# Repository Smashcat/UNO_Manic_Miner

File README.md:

# Arduino UNO Game Engine
Manic Miner, Scramble and Space Invaders on the Arduino UNO with composite output

This is a project to demonstrate the use of my game engine, with a port of Manic Miner, originally for the ZX Spectrum, by Matthew Smith, and the original Scramble and Space Invaders arcade machine, it also now has the console game Pacman Championship Edition. Please note that this is for the original Arduino UNO with the ATMega328P microcontroller - it will not work on any other versions of the Arduino. Also, some of the cheaper "Arduino compatible" boards use resonators instead of crystals for their clock. These are nowhere near accurate enough to generate the video signal. I have tried several and it caused extreme jitter in the image. If you can, use an official Arduino, or at least a board with a proper 16Mhz crystal!!

## Engine Features:

+ Composite output using 2 resistors
+ Scrolling tilemap background
+ Up to 9 16x16 sprites on screen, with up to 7 per scanline
+ 1 sprite has pixel-perfect collision detection against other sprites
+ Fixed framerate of 50fps
+ Effective resolution is 256x256 (no framebuffer, everything is generated by "racing the beam")
+ Lots of spare cycles, enough to run game logic and easily update sprite positions, and even all tile indexes on screen every frame!

## PCB Features:
  
+ PCB design schematics for a shield for the Arduino UNO, with buttons, composite output, speaker driving circuit and a an area to mount a Nintendo NES controller port to use instead of the buttons
+ All files for PCB, including production files ready to place a fully assembled order (except for the NES port and header pins) from JLCPCB. Cost including delivery per board for 20 fully assembled boards seems to be around £4 for me in the UK.

## Manic Miner Game Features:

+ All 20 original levels
+ All "special" boss and other mechanics. Including Eugene, the Kong Beast, Skylab crashing enemies and Solar Generator beam
+ Extra animation on final cavern level showing realtime tile animation
+ Menu screen with options to choose start level, turn music on/off and reset high score which is persistant between boots
+ 2 channel audio with original music
+ Special end screen and message if you complete the game!

## Space Invaders Game Features:

+ Pixel perfect recreation of original graphics
+ Gameplay logic matches the original game
+ Persistant high score (can be reset by holding Option+Start at boot)
+ 2 Channel Audio

## Scramble Game Features

+ Level data from original ROMs
+ Gameplay logic matches original game
+ Smooth pixel scrolling, with fixed starfield in background
+ Persistant high score (can be reset by holding Start at boot)
+ 2 Channel Audio

## Pacman Championsip Edition Features

+ Fast moving gameplay with smooth pixel scrolling
+ Optimized graphics for the 1-bit display
+ 2 Channel PWM audio, with sound effects closely matching original Pacman game
+ High score list (hold SELECT+START at power on to reset list)
+ [WebASM demo available! ](https://www.smashcat.org/pacman-ce/)

## YouTube:

## Screen-shots:

### CRT monitor:

### TFT TV screen:

### PCB shield with NES controller

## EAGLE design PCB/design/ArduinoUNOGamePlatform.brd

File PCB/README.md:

# Arduino UNO Manic Miner

Composite output shield for Arduino UNO

This folder contains the files for the PCB that can be used with this project.

+ ./design - the Eagle design files
+ ./images - Schematic and board images
+ ./production-files - These can be used to have the PCB fully assembled at JLCPCB. If using another service, the gerbers should be compatible.

I have also linked sources I used for the NES controller and port that can be soldered to the PCB, below. Also the 3 pin jack to 2 x RCA cable I use for video and audio connection from the PCB to my TV/monitors. I'm not sponsored by anyone, just thought these might be handy!

## NES port compatible with the PCB:

## NES controller (aftermarket) - make sure you pick the "nes white" or "nes grey" version, NOT the "classic mini" version!:

## 3-pin 3.5mm jack to 2xRCA male cable:

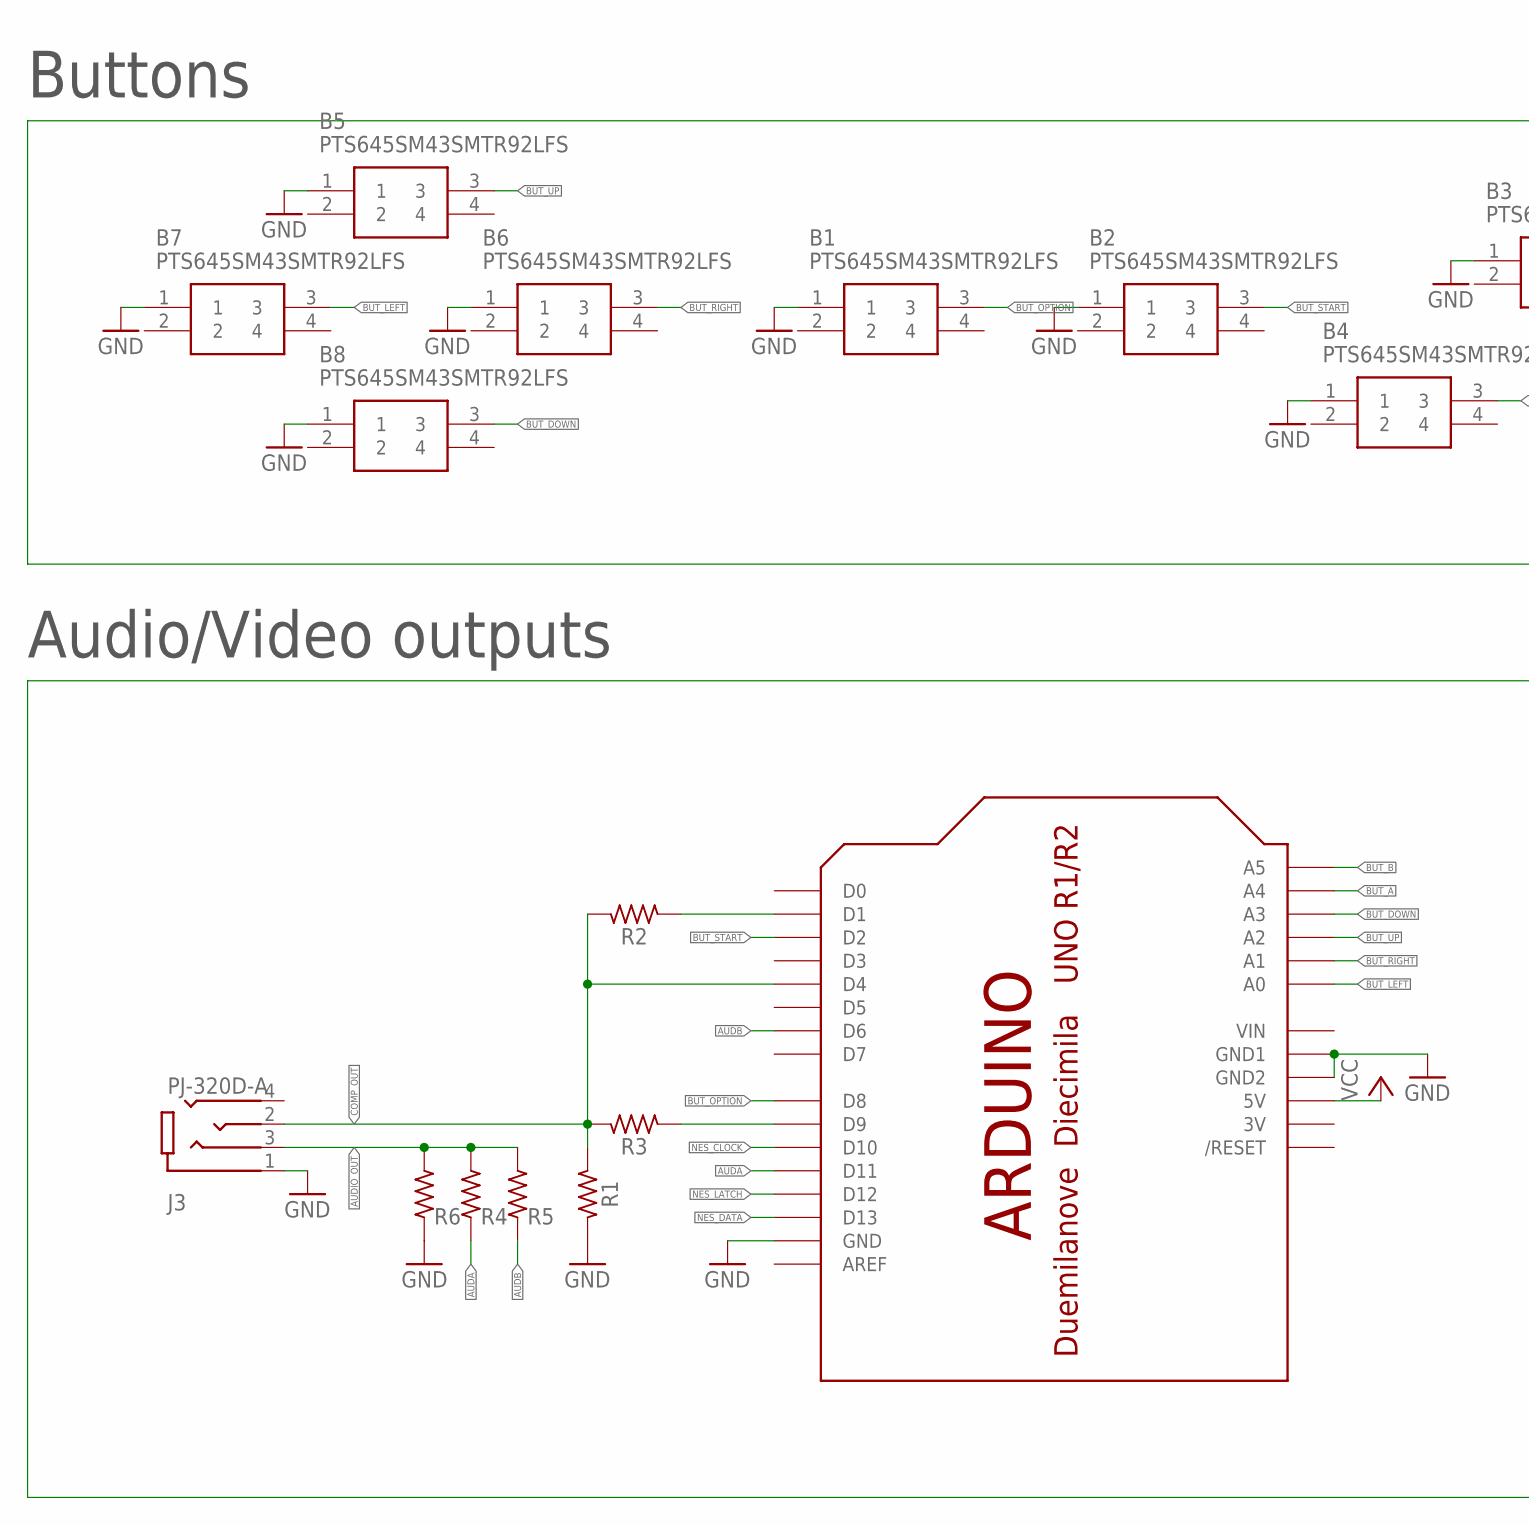
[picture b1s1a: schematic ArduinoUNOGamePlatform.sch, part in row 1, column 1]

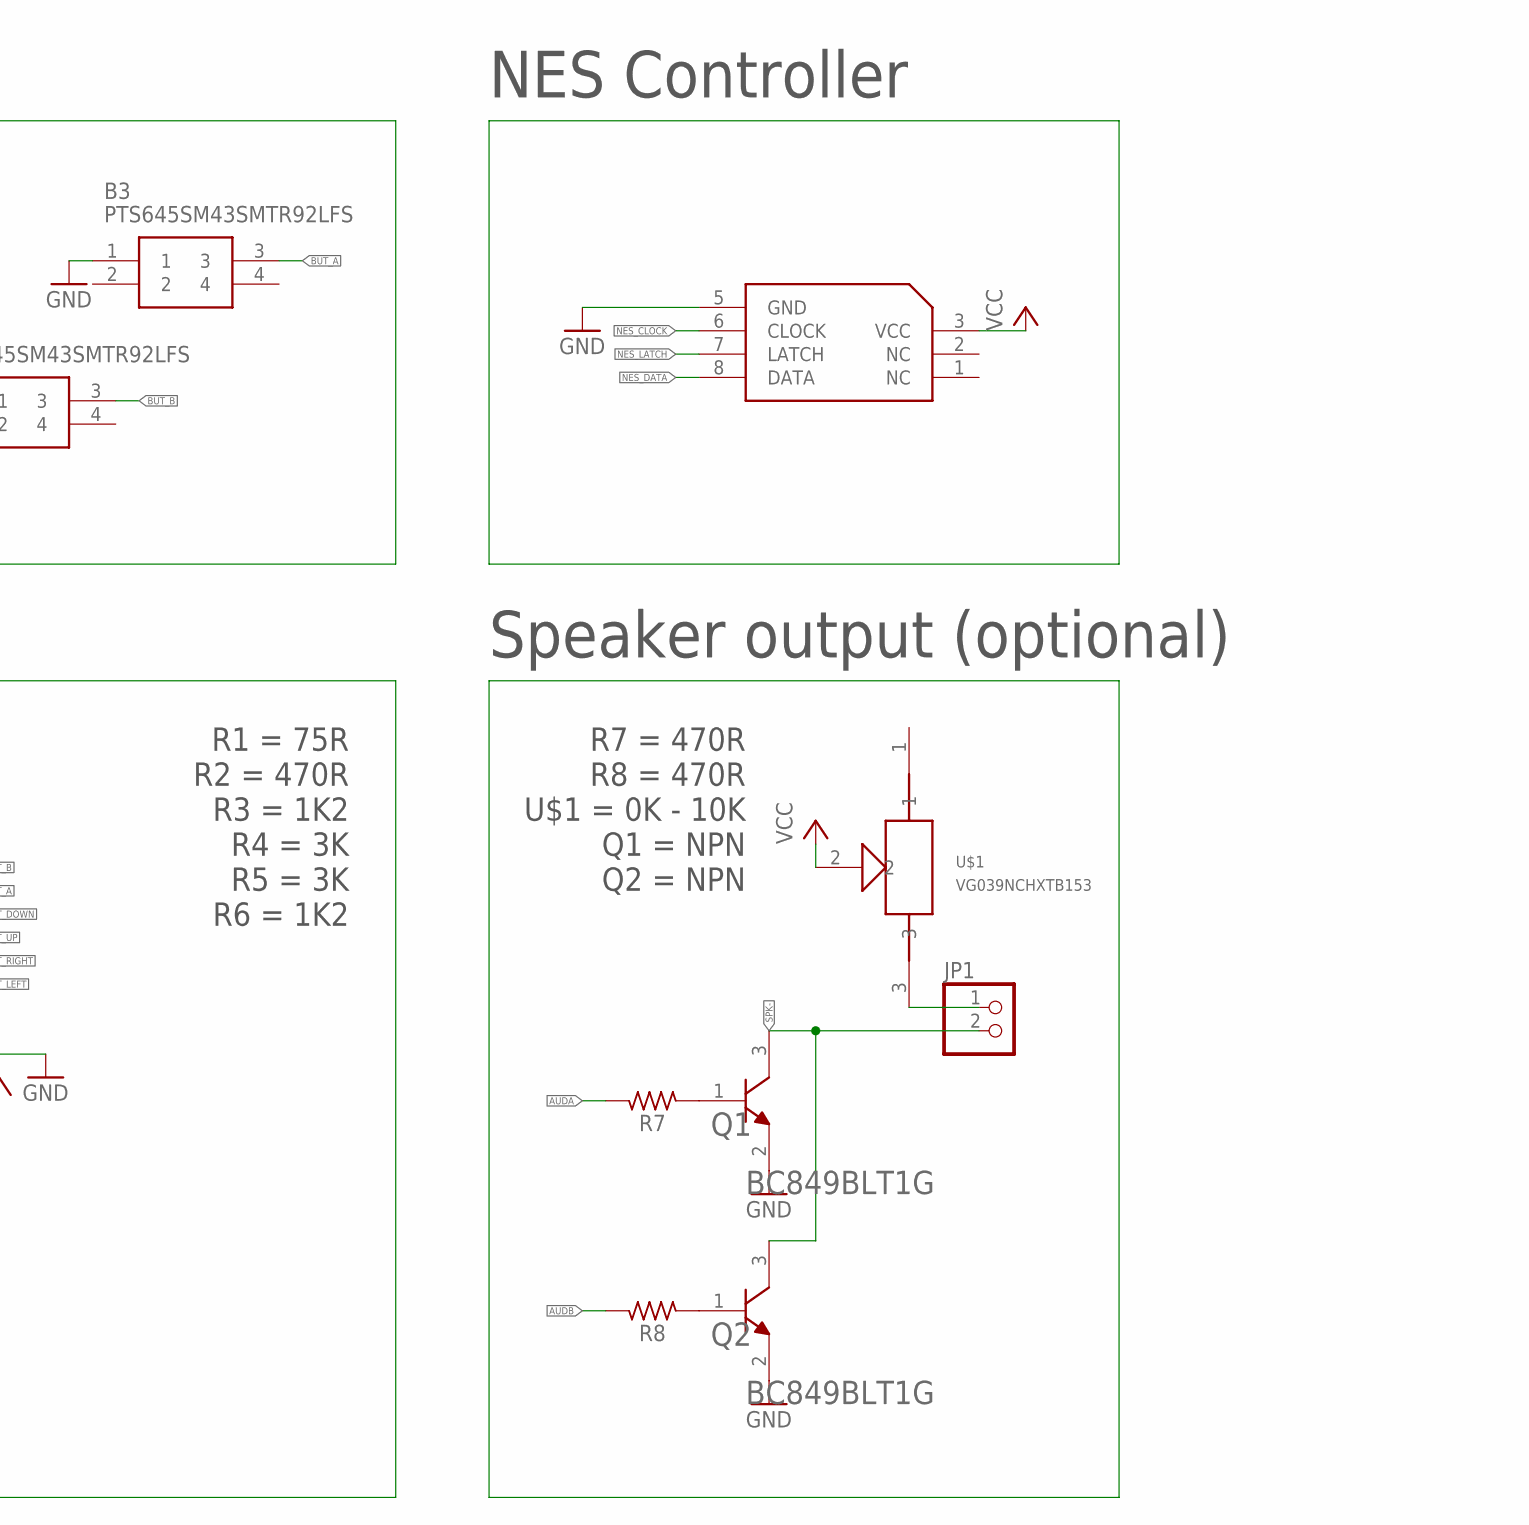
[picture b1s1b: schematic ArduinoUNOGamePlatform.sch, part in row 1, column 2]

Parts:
B1, B2, B3, B4, B5, B6, B7, B8: PTS645SM43SMTR92LFS; PTS645(SMT)
J3: PJ-320D-A; HRO_PJ-320D-A
JP1: PINHD-1X2; 1X02
Q1, Q2: ON_SEMICONDUCTOR_BC849BLT1GON_SEMICONDUCTOR_BC849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; ON_SEMICONDUCTOR_BC849BLT1G_0
R1: 75R; 52101-101-REV-A_RC-MASTER-SMD_R0603MP
R2: 220R; 52101-101-REV-A_RC-MASTER-SMD_R0603MP
R3, R6: 1K2; 52101-101-REV-A_RC-MASTER-SMD_R0603MP
R4, R5: 3K; 52101-101-REV-A_RC-MASTER-SMD_R0603MP
R7, R8: 470R; 52101-101-REV-A_RC-MASTER-SMD_R0603MP
U$1: VG039NCHXTB153; VG039NCHXTB101
U$2: ARDUINO-BPLACE
U$3: NES-CONTROLLER-PORT; NES-CONTROLLER-SOCKET

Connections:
3V: U$2.3V
AUDA: R4.1, R7.2, U$2.D11
AUDB: R5.1, R8.2, U$2.D6
AUDIO_OUT: J3.3 (RING1), R4.2, R5.2, R6.1
BUT_A: B3.3, U$2.A4
BUT_B: B4.3, U$2.A5
BUT_DOWN: B8.3, U$2.A3
BUT_LEFT: B7.3, U$2.A0
BUT_OPTION: B1.3, U$2.D8
BUT_RIGHT: B6.3, U$2.A1
BUT_START: B2.3, U$2.D2
BUT_UP: B5.3, U$2.A2
COMP_OUT: J3.2 (TIP), R1.1, R2.2, R3.2, U$2.D4
GND: B1.1, B2.1, B3.1, B4.1, B5.1, B6.1, B7.1, B8.1, J3.1 (SLEEVE), Q1.2 (E), Q2.2 (E), R1.2, R6.2, U$2.GND, U$2.GND1, U$2.GND2, U$3.5 (GND)
unnamed: JP1.1, U$1.3
unnamed: Q2.1 (B), R8.1
unnamed: Q1.1 (B), R7.1
NES_CLOCK: U$2.D10, U$3.6 (CLOCK)
NES_DATA: U$2.D13, U$3.8 (DATA)
NES_LATCH: U$2.D12, U$3.7 (LATCH)
SPK-: JP1.2, Q1.3 (C), Q2.3 (C)
SYNC_OUT: R3.1, U$2.D9
VCC: U$1.2, U$2.5V, U$3.3 (VCC)
VIDEO_OUT: R2.1, U$2.D1
VIN: U$2.VIN

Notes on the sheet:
Buttons
Audio/Video outputs
NES Controller
Speaker output (optional)
R1 = 75R R2 = 470R R3 = 1K2 R4 = 3K R5 = 3K R6 = 1K2
R7 = 470R R8 = 470R U$1 = 0K - 10K Q1 = NPN Q2 = NPN

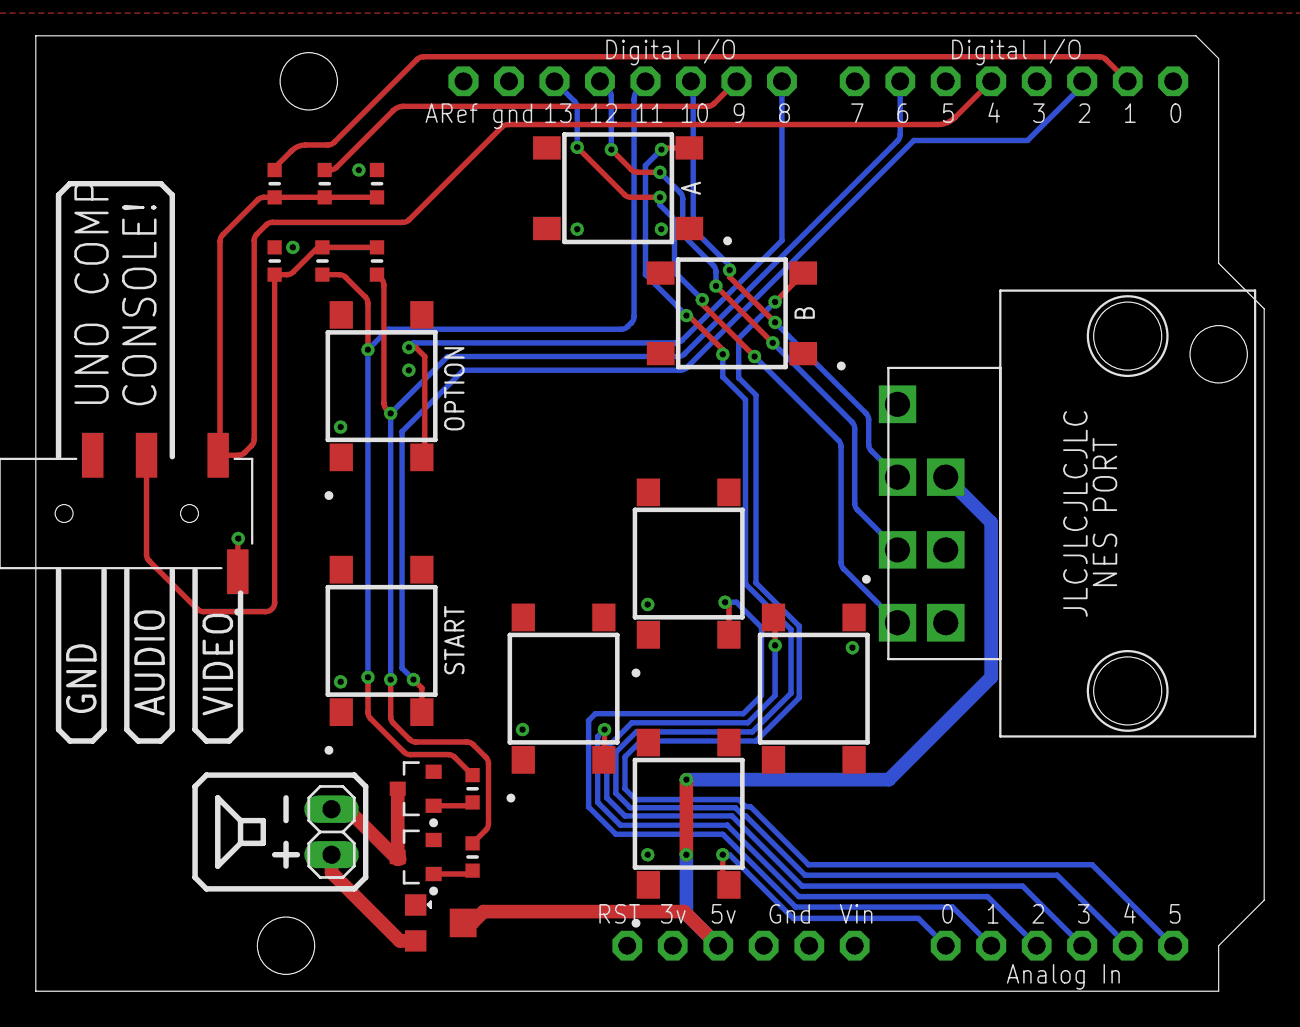
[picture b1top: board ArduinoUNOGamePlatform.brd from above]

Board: 2 copper layers, 68.6 x 53.3 mm, 23 parts (0 on the bottom side), 23 nets.

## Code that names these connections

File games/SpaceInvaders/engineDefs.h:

/*
 
 This file is part of Manic Miner for Arduino UNO.
 Copyright (C) 2024 Scott Porter

 Manic Miner for Arduino UNO is free software: you can redistribute it and/or modify
 it under the terms of the GNU General Public License as published by the Free Software 
 Foundation, either version 3 of the License, or (at your option) any later version.

 This program is distributed in the hope that it will be useful, but WITHOUT ANY WARRANTY; 
 without even the implied warranty of MERCHANTABILITY or FITNESS FOR A PARTICULAR PURPOSE.
 See the  GNU General Public License for more details.

 You should have received a copy of the GNU General Public License
 along with this program.  If not, see <http://www.gnu.org/licenses/>

 */

#ifndef __ENGINE_DEFS
#define __ENGINE_DEFS

// If using NES controller, set this to 1, otherwise 0 for normal buttons. If you want to connect a controller to the
// header pins, then use the defines beginning with "NES_" below. These are all on the B port (add 8 to each one to find its "D" number on the UNO board)
#define USE_CONTROLLER          1

// Currently the engine supports up to 9 16x16 sprites on screen at once. With up to 7 in any one line, which is, again, ideal for Manic Miner.
// Sprite 8 (the last one) is a special player sprite. It also does pixel-based collision detection with the other sprites and sets or clears the collision flag
// each frame.
#define NUM_SPRITES             4

// Can be longer than the raster line if horizontal scrolling needs to be really fast. Just allows for move offscreen pixels to be written
#define BYTES_PER_BUFFER_LINE   32

// Horizontal pixels per tile - usually 8 (tiles are always 8 pixels wide)
#define PIXELS_PER_CHARACTER    8

// Vertical rows in tiles. Default is 32, for 256 pixels vertically
#define CHARACTER_ROWS          32

// Nothing else should be changed from here down, unless you want to change input pins, or modify code etc.

#define MUTE_PWM_0            DDRD&=~(1<<6)
#define UNMUTE_PWM_0          DDRD|=(1<<6)

#define MUTE_PWM_1            DDRB&=~(1<<3)
#define UNMUTE_PWM_1          DDRB|=(1<<3)

#if USE_CONTROLLER

#define BUTTON_RIGHT          (1<<0)
#define BUTTON_LEFT           (1<<1)
#define BUTTON_DOWN           (1<<2)
#define BUTTON_UP             (1<<3)
#define BUTTON_START          (1<<4)
#define BUTTON_OPTION         (1<<5)
#define BUTTON_B              (1<<6)
#define BUTTON_A              (1<<7)

#define NES_DATA              5
#define NES_LATCH             4
#define NES_CLOCK             2

#else

#define BUTTON_B              (1<<5)
#define BUTTON_A              (1<<4)
#define BUTTON_DOWN           (1<<3)
#define BUTTON_UP             (1<<2)
#define BUTTON_RIGHT          (1<<1)
#define BUTTON_LEFT           (1<<0)
#define BUTTON_START          (1<<6)
#define BUTTON_OPTION         (1<<7)

#endif

#define PRESSING_START        ((keyState.current&BUTTON_START)==0)
#define PRESSING_OPTION       ((keyState.current&BUTTON_OPTION)==0)
#define PRESSING_A            ((keyState.current&BUTTON_A)==0)
#define PRESSING_B            ((keyState.current&BUTTON_B)==0)
#define PRESSING_LEFT         ((keyState.current&BUTTON_LEFT)==0)
#define PRESSING_RIGHT        ((keyState.current&BUTTON_RIGHT)==0)
#define PRESSING_UP           ((keyState.current&BUTTON_UP)==0)
#define PRESSING_DOWN         ((keyState.current&BUTTON_DOWN)==0)
#define NOTHING_PRESSED       (keyState.current==0xff)

// If zero, no horizontal scrolling code is included for the tilemap.
#define USE_MASK        0

// If any of these are 0, then sprite will overwrite sprites under it instead of ORing with them. Improves performance quite a bit for sprites that don't overlap!
// Sprites are always ORd with the background tiles
#define OR_SPRITE0      1
#define OR_SPRITE1      1
#define OR_SPRITE2      1
#define OR_SPRITE3      1
#define OR_SPRITE4      1
#define OR_SPRITE5      1
#define OR_SPRITE6      1
#define OR_SPRITE7      1

// If set to 0, then sprite can only move in the vertical axis, or if moving horizontally, can only be 8 pixels wide, or will clip as it moves. Improves performance 
// for games where some sprites are only 8 pixels or less wide
#define V_SPRITE0       1
#define V_SPRITE1       0
#define V_SPRITE2       0
#define V_SPRITE3       0
#define V_SPRITE4       1
#define V_SPRITE5       1
#define V_SPRITE6       1
#define V_SPRITE7       1

// Always 32 for current renderer for 256 pixels horizontally
#define BYTES_PER_RASTER 32

// Pin used to prevent the UART from outputting a pixel as it is enabled at the start of the scanline. Unfortunately there's not really any other way to do this
#define PIN_SUPPRESS 4

// Pin used to signal the v/h-sync period. Do not change. It's actually PORTB, bit 1
#define PIN_SYNC 9

// There is one extra tile in x and y to allow for smooth scrolling without glitches
#define SCREEN_RAM_SIZE ((BYTES_PER_BUFFER_LINE) * (CHARACTER_ROWS))

// time into scanline when pixel pumper awakes (but it takes time to get going because of the interrupt handler etc.
// Units: us * 16
#define LEFT_EDGE 212
// scan line at which pixel pumper is enabled. 30 minimum to be on-screen on 7-inch monitor
#define TOP_EDGE 48
// and when it's stopped. 303 maximum to be on-screen on 7-inch monitor - you can subtract 1 here to hide the bottom row of tiles for smoother vertical scrolling
#define BOTTOM_EDGE (TOP_EDGE + (CHARACTER_ROWS-1) * PIXELS_PER_CHARACTER)

#define PROCESSED_SPRITE_OFFSET     200

#endif

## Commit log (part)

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2024-03-10 Create LICENSE
2024-03-10 Initial file commit - copied from dev
2024-03-10 Added schematic image
2024-03-10 Added GPL license, fixed bug allowing Willy to walk into wall if he landed within a pixel after jump
2024-03-10 Added some screen-shots
2024-03-12 Update README.md
    Added text about need to use original arduino, and not the cheap boards with resonators instead of proper crystals.
2024-03-13 Fixed some stale comments and removed commented out old code. Changed some resistor values on PCB following testing. Added designation to move order number under the NES port if using JLC to produce 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
2024-03-14 Updated schematic to match design files
2024-03-14 Updated resistor values in BOM
2024-03-14 Updated README with couple of screen-shots from a TFT TV
2024-03-14 Modified PCB design to make it easier for hand-soldering, and also changed to better buttons
2024-03-15 Reduced code size slightly, found issue if debug.h is removed - something to do with how Arduino IDE includes Serial.print() functions. Please leave it included, even though the functions are not cal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
2024-03-15 Further code size reductions. Slowed down flashing of options in menu, added compiled binaries in case it helps people flashing to non-arduino ATMega328 based boards
2024-03-15 Updated PCB design to modify NES port part. Holes were too tight and not enough clearance for it under board, so now on top. Also pins moved slightly further apart to make soldering a little easier
2024-03-16 Added NES controller support
2024-03-16 Decided to move the pins used for the controller to unused pins on PORTB so that buttons could be used in addition, in future games. Also modified input a little to controller reading. New PCB images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
2024-03-16 Renamed images to flush cache on github
2024-03-19 Added sources for NES controller and port for the PCB
2024-03-19 Updated image links to new github format
2024-03-19 Added Amazon link to cable from PCB to TV/monitor
2024-03-19 Made the text cleared around picking the correct controller type from Aliexpress
2024-03-21 Added photo of shield with NES controller
2024-04-01 Added Space Invaders game!
2024-04-01 Renamed image
2024-04-01 Added a couple more screen-shots of Space Invaders
2024-04-11 Added basic scrolling example, with comments
2024-04-13 Fixed horizontal scrolling issues with jitter and updated scrolling example. Updates not currently in space invaders and manic miner games.
2024-04-26 Made the scrolling demo a bit more interesting
2024-05-11 Added Scramble!
2024-05-12 Code cleanup. Moved all remaining constant data to the gameAssets.h (autogenerated from original data, PNGs, plus extra arrays)
2024-05-12 Update issue templates
